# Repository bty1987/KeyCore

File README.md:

<div align="center">

# KeyCore · 磁轴透明屏幕键盘

**67 键磁悬浮轴体 · 13.3" 屏下显示 · 无机械轴 · 全开源**

`磁轴键盘` `Hall Effect` `ESP32-S3` `Transparent Keyboard` `Flux Keyboard 复刻` `嘉立创EDA`

*Finalmouse/Flux 式屏下键盘的国产开源复刻与再设计*

**屏下显示最终效果** —— 13.3" 屏幕实际显示画面：67 键位图 · 按键按下高亮 · 大时钟动效
（预览页 [keymap.html](04-显示层/keymap.html)，正式版为定制全屏程序）

<br clear="all" />

**PCB v43b-5c 封板版布线** —— 300×192mm 四层（L1 红 / L2 蓝 / GND+3V3 平面）：67 霍尔 · 9×74HC4051 · ESP32-S3 · DRC 全绿

</div>

---

## 📖 这是什么

一块 **300×192mm 的透明键盘**：PCB 上密布 67 颗霍尔传感器，键帽底部嵌磁铁，
按下时磁场变化被感应——**没有机械轴体，按压行程就是磁场行程**。
键盘上方悬浮一块 13.3" 1080P 屏幕（屏下键盘结构），显示内容完全可编程。

灵感来自 [Finalmouse x Wooting 的 Flux Keyboard](01-方案/竞品拆解-FluxKeyboard.md)，
本项目是其国产化开源复刻 + 再设计：磁路自主设计、电子自主绘制、结构参数化生成。

```
┌─────────────────────────────────────┐
│   13.3" 透明屏（显示：键位/宏/动画）  │ ← z 7.2+
│─────────────────────────────────────│
│   透明厚板 9mm（67 键孔打穿+磁道）    │ ← z 10.7+
│─────────────────────────────────────│
│   PCB 300×192 4层                    │
│   67×霍尔 + 9×多路开关 + ESP32-S3    │ ← z 0~1.6
│─────────────────────────────────────│
│   底壳（USB-C/背墙通道/12V）          │
└─────────────────────────────────────┘
   按压 → 键帽磁铁靠近霍尔 → ADC 采样 → 触发
```

## ✨ 核心特性

- **磁轴无接触**：HAL49ESO 霍尔 ×67，模拟量采样 → 触发力度/行程软件可调（类 Wooting 模拟轴）
- **9× 74HC4051 分时复用**：67 路模拟信号仅占 1 个 ADC 通道 + 12 个控制脚
- **4 层板电源架构**：内层整平面 GND/3V3 + 191 个缝合孔，67 颗霍尔供电零妥协
- **结构全参数化**：键位表 → OpenSCAD → 厚板 CNC 图纸 / 订购图，改键位即改结构件
- **屏下显示可编程**：定制全屏程序（非浏览器方案），显示键位图/宏状态/力度可视化

## 📊 关键参数

| 项 | 规格 |
|---|---|
| 配列 | 65% 标准配列 61 键 + 宏 M1~M6（共 67） |
| 主控 | ESP32-S3-WROOM-1-N4R8（4MB Flash + 8MB Octal PSRAM, WiFi+BLE） |
| 传感 | HAL49ESO 线性霍尔 ×67（SOT-23，1.9mm 间距采样） |
| 采样链 | 74HC4051 ×9（MUX_A/B/C 地址 + EN_1~9 使能）→ ESP32 ADC |
| PCB | 300.2 × 192 × 1.6mm，4 层（TOP/In1-GND/In2-3V3/BOT），JLC 有铅喷锡 |
| 结构 | 透明亚克力厚板 300.2×192×9mm，67 键孔打穿 + 73 条磁道（CNC） |
| 显示 | 13.3" IPS 1080P（300.2×187.4×2.5mm，HDMI 驱动板 / 计划 Orange Pi 直驱） |
| 接口 | USB-C（数据+5V）、UART 排针、DS18B20 温度探头座、12V 屏供电 |
| 触发 | 磁铁 4×2×2 N52 ×2/键 嵌键帽侧壁（磁路 v5.3，P0′ 实测待做） |

## 🗂 仓库结构

```
KeyCore/
├── 00-文档/          # 项目文档（v3.0 时代已标注存档）
├── 01-方案/          # 方案演进（Flux 竞品拆解、侧磁方案决策）
├── 02-结构图纸/      # ★ OpenSCAD 参数化结构（厚板 v4 / 底壳 / 键位表 CSV）
├── 03-固件/          # ESP32 固件工程（P0 验证完成，正式固件开发中）
├── 04-显示层/        # 屏幕显示页（键位图/坏点测试）
├── 06-测试记录/      # P0 磁路实测数据与报告
├── 07-PCB/           # ★ PCB 交付物（Gerber/打板清单/BOM/全程总结）
│   ├── footprints/   #   封装库
│   ├── tools/        #   处理脚本（历史 KiCad 管线，已退役）
│   └── output/       #   ★★ 所有交付文档都在这里
└── 99-归档/          # 历史方案存档
```

## 📍 项目状态

```mermaid
timeline
    title KeyCore 研发时间线
    2026-09 : 磁路 P0 单键验证 → PASS（隔屏 Δ+1023mV）
    2026-10 上旬 : 侧磁方案 v5.0 定稿 · PCB 300×192 四层布线完成
    2026-10-08 : Gerber 锁定 · 嘉立创下单（5 片全贴 ¥1235）
    2026-10-14 : PCB 到货 → 收板自检（自检固件就绪）
    下一步 : 上电自检 → 固件开发 · 厚板 CNC · 磁轴 P0′ 实测 · 整机合装
```

<details>
<summary><b>已完成里程碑</b>（点击展开）</summary>

- ✅ **P1 屏幕验收**：13.3" 屏 + 驱动板点亮，实测三围与显示区
- ✅ **P0 磁路验证**：隔屏检测可行、极性双向响应、邻域噪声 ±4mV（`06-测试记录/`）
- ✅ **BOM 闭环**：105 元件全部绑定立创 C 号，封装逐项对照商城实物核验
- ✅ **机械定稿**：PCB 300×192 = 厚板同宽 = 屏幕同宽三件套对齐；键位坐标 EDA 实测基准
- ✅ **布线**：FreeRouting 全局布线（GND/3V3 走内层平面 + 191 缝合孔），DRC 仅剩 1 项已接受项
- ✅ **下单**：订单 Y4，生产稿已确认，10-13 发货

</details>

## 🛠 技术栈与工具链

| 层 | 工具 |
|---|---|
| EDA | 嘉立创EDA专业版 4.1.60 + [easyeda-agent](https://github.com/zhoushoujianwork/easyeda-agent) CLI 自动化 |
| 布线 | FreeRouting 1.9.0（DSN 剔除电源网 → SES 回导） |
| 结构 | OpenSCAD（参数化：键位 CSV → 板/壳/订购图） |
| 固件 | PlatformIO + arduino-esp32 / ESP-IDF |
| 验证 | Gerber 机检脚本 · DRC 双口径（几何终审 + 引擎审计） |

## 📚 权威文档（新读者按此顺序读）

1. [画线总结-过程与经验](07-PCB/output/画线总结-过程与经验-20261008.md) —— 全流程 SOP + 18 条踩坑 + 费用实测
2. [设计说明-KeyCore总装](07-PCB/output/设计说明-KeyCore总装-20261007.md) —— 层叠/分区/引脚定稿
3. [打板清单](07-PCB/output/打板清单-KeyCore-v43b-3c-20261008.md) —— BOM 14 项 C 号 + 自留件 + 费用
4. [thickplate-v4.scad](02-结构图纸/thickplate-v4.scad) —— 厚板加工源（67 孔打穿版）

## 💰 成本实况

| 阶段 | 花费 |
|---|---|
| P0/P1 验证（屏+霍尔+磁铁样品） | ~¥470 |
| PCB 4 层 ×5 + SMT 全贴（本单） | ¥1235.19 |
| 厚板 CNC（待下） | 预估 ¥100~200 |
| **首台物料合计** | **~¥2000**（定型后单台 BOM ≈¥1250） |

## 🗺 Roadmap

- [x] P0 磁路验证 · P1 屏幕验收
- [x] PCB 布线 + 下单（v43b-3c）· 收板（10-14）
- [ ] **上电自检**（清单+固件就绪：[收板上电自检](06-测试记录/收板上电自检-20261014.md)）→ 固件（octal PSRAM / 霍尔扫描 / USB HID）
- [ ] 厚板 CNC 下单（图纸就绪：[厚板订购图 V6r](07-PCB/output/厚板订购图-V6-打穿版-20261007.svg)）
- [ ] 磁轴 P0′ 三项实测（回弹/串扰/隔屏Δ）→ 键帽块 P3 设计
- [ ] 屏幕方案落地（Orange Pi Zero 2W + 定制全屏程序）
- [ ] v2 候选：74HC4067 精简（9→5 颗）· ESP32-P4 直驱屏幕 · N16R8V 模组

## 🤝 说明

- 本项目为个人研发项目，过程文档全量保留（包括失败与返工），供同样想做磁轴键盘的玩家参考
- 复刻请重读 [画线总结](07-PCB/output/画线总结-过程与经验-20261008.md) 的"踩坑全集"——每一条都是真实返工换来的
- 嘉立创按图生产不纠错：**DFM 放行 ≠ 设计正确**，正确性唯一来源是数据手册比对与实测

---

<div align="center">

*键盘的尽头是磁场 · Magnetic or nothing*

</div>

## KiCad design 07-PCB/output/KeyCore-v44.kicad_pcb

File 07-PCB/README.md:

# 07-PCB · PCB 工作目录

> **⚠ 2026-10-08 更新**：KiCad 程序化生成管线（tools/ 下的 emit_v4x 等）为历史方案，**现行流程 = 立创EDA 专业版 + easyeda-agent CLI**（FreeRouting 全局布线）。KiCad 管线退役存档于 git 历史。

## 现行状态

- **工程**：KeyCore-v43b-3c（立创EDA，4 层 300×192mm）
- **已下单**：订单 Y4 / SMT2610080582（¥1235.19，5 片全贴，2026-10-13 发货）
- **Gerber**：`output/gerber_3c/KeyCore-v43b-3c-JLC-Order.zip`（18 文件，唯一有效下单包）
- **打板清单**：`output/打板清单-KeyCore-v43b-3c-20261008.md`
- **全程经验**：`output/画线总结-过程与经验-20261008.md`（SOP/踩坑/费用实测）

## 目录

- `footprints/` — KiCad 封装库（早期 KiCad 管线产物，留作参考）
- `tools/` — 退役的 KiCad/SES 处理脚本（git 历史有效，本地可删）
- `output/` — 全部交付物（Gerber/清单/图纸/总结）

## 坐标权威

**EDA live 霍尔位 = 唯一权威**（CSV v5.2 的 x/y 已过时，仅 w_u 键宽列可用）。孔心=霍尔位（2026-10-07 拍板，+4 预放偏置弃用）。

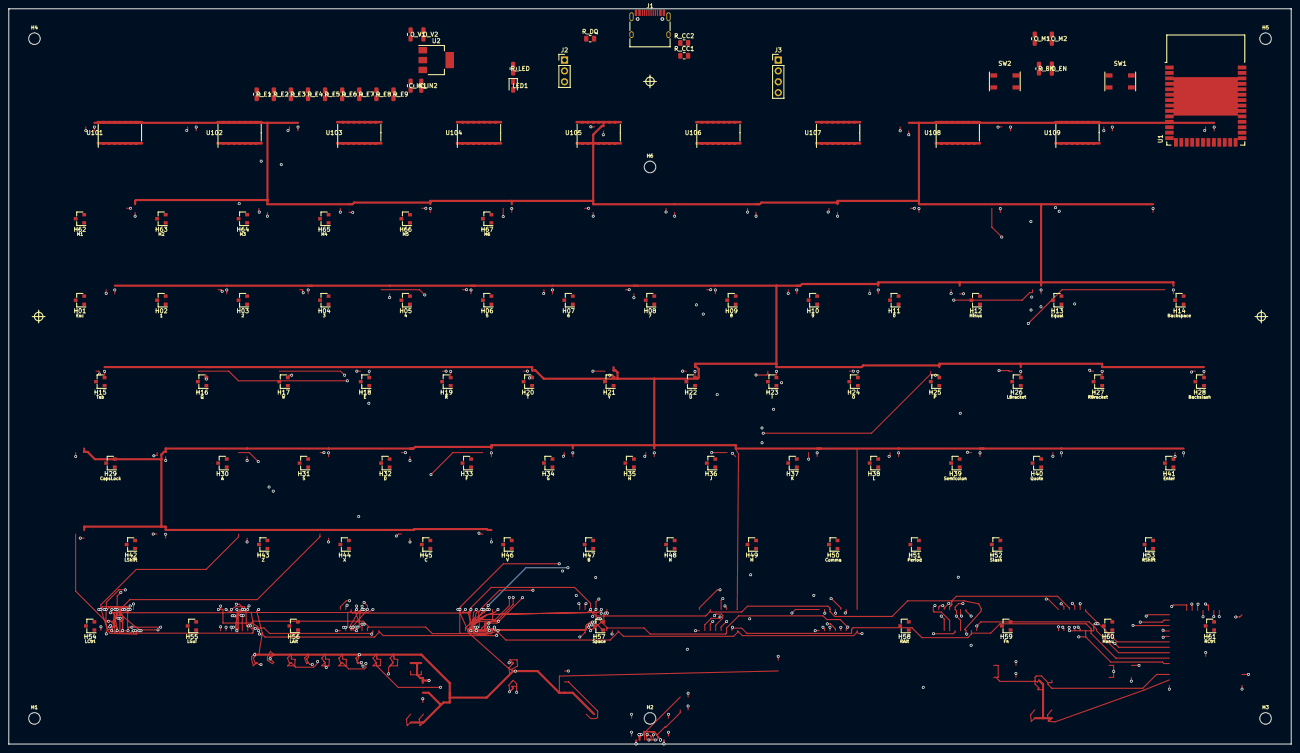
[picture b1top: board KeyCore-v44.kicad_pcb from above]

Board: 4 copper layers, 300.0 x 172.0 mm, 111 parts (0 on the bottom side), 94 nets.

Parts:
C_EN: 10uF; C_0805_2012Metric
C_IN1: 10uF; C_0805_2012Metric
C_IN2: 0.1uF; C_0805_2012Metric
C_M1: 10uF; C_0805_2012Metric
C_M2: 0.1uF; C_0805_2012Metric
C_V1, C_V2: 22uF; C_0805_2012Metric
H01, H02, H03, H04, H05, H06, H07, H08, H09, H10, H11, H12, H13, H14, H15, H16, H17, H18, H19, H20, H21, H22, H23, H24, H25, H26, H27, H28, H29, H30, H31, H32, H33, H34, H35, H36, H37, H38, H39, H40, H41, H42, H43, H44, H45, H46, H47, H48, H49, H50, H51, H52, H53, H54, H55, H56, H57, H58, H59, H60, H61, H62, H63, H64, H65, H66, H67: HAL49E; SOT-23
H1, H2, H3, H4, H5, H6: MountingHole_2.7mm
J1: USB-C 16P; USB_C_Receptacle_HRO_TYPE-C-31-M-12
J2: DS18B20; PinHeader_1x03_P2.54mm_Vertical
J3: UART1; PinHeader_1x04_P2.54mm_Vertical
LED1: PWR; LED_0805_2012Metric
R_CC1, R_CC2: 5.1K; R_0805_2012Metric
R_DQ: 4.7K; R_0805_2012Metric
R_E1, R_E2, R_E3, R_E4, R_E5, R_E6, R_E7, R_E8, R_E9: 10K; R_0805_2012Metric
R_EN: 10K; R_0805_2012Metric
R_LED: 1K; R_0805_2012Metric
SW1: BOOT; Button_Switch_TS-1187A
SW2: EN; Button_Switch_TS-1187A
U1: ESP32-S3-WROOM-1-N4; ESP32-S3-WROOM-1
U2: AMS1117-3.3; SOT-223-3_TabPin2
U101, U102, U103, U104, U105, U106, U107, U108, U109: 74HC4051; SOIC-16_3.9x9.9mm_P1.27mm

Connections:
3V3: C_M1.1, C_M2.1, C_V1.1, C_V2.1, H01.1, H02.1, H03.1, H04.1, H05.1, H06.1, H07.1, H08.1, H09.1, H10.1, H11.1, H12.1, H13.1, H14.1, H15.1, H16.1, H17.1, H18.1, H19.1, H20.1, H21.1, H22.1, H23.1, H24.1, H25.1, H26.1, H27.1, H28.1, H29.1, H30.1, H31.1, H32.1, H33.1, H34.1, H35.1, H36.1, H37.1, H38.1, H39.1, H40.1, H41.1, H42.1, H43.1, H44.1, H45.1, H46.1, H47.1, H48.1, H49.1, H50.1, H51.1, H52.1, H53.1, H54.1, H55.1, H56.1, H57.1, H58.1, H59.1, H60.1, H61.1, H62.1, H63.1, H64.1, H65.1, H66.1, H67.1, J2.1, J3.3, LED1.1, R_DQ.2, R_E1.2, R_E2.2, R_E3.2, R_E4.2, R_E5.2, R_E6.2, R_E7.2, R_E8.2, R_E9.2, R_EN.2, U1.2, U2.2, U101.16, U102.16, U103.16, U104.16, U105.16, U106.16, U107.16, U108.16, U109.16
BOOT: SW1.1, SW1.2, U1.27
CC1: J1.A5, R_CC1.1
CC2: J1.B5, R_CC2.1
EN: C_EN.1, R_EN.1, SW2.1, SW2.2, U1.3
EN_1: R_E1.1, U1.12, U101.6
EN_2: R_E2.1, U1.17, U102.6
EN_3: R_E3.1, U1.18, U103.6
EN_4: R_E4.1, U1.19, U104.6
EN_5: R_E5.1, U1.20, U105.6
EN_6: R_E6.1, U1.21, U106.6
EN_7: R_E7.1, U1.22, U107.6
EN_8: R_E8.1, U1.8, U108.6
EN_9: R_E9.1, U1.9, U109.6
GND: C_EN.2, C_IN1.1, C_IN2.1, C_M1.2, C_M2.2, C_V1.2, C_V2.2, H01.2, H02.2, H03.2, H04.2, H05.2, H06.2, H07.2, H08.2, H09.2, H10.2, H11.2, H12.2, H13.2, H14.2, H15.2, H16.2, H17.2, H18.2, H19.2, H20.2, H21.2, H22.2, H23.2, H24.2, H25.2, H26.2, H27.2, H28.2, H29.2, H30.2, H31.2, H32.2, H33.2, H34.2, H35.2, H36.2, H37.2, H38.2, H39.2, H40.2, H41.2, H42.2, H43.2, H44.2, H45.2, H46.2, H47.2, H48.2, H49.2, H50.2, H51.2, H52.2, H53.2, H54.2, H55.2, H56.2, H57.2, H58.2, H59.2, H60.2, H61.2, H62.2, H63.2, H64.2, H65.2, H66.2, H67.2, J1.A1, J1.A12, J1.B1, J1.B12, J1.S1, J2.3, J3.4, R_CC1.2, R_CC2.2, SW1.3, SW1.4, SW2.3, SW2.4, U1.1, U1.40, U1.41, U2.1, U101.7, U101.8, U102.7, U102.8, U103.7, U103.8, U104.7, U104.8, U105.7, U105.8, U106.7, U106.8, U107.7, U107.8, U108.7, U108.8, U109.7, U109.8
HO_K01: H01.3, U103.13
HO_K02: H02.3, U103.14
HO_K03: H03.3, U103.15
HO_K04: H04.3, U103.12
HO_K05: H05.3, U103.1
HO_K06: H06.3, U103.5
HO_K07: H07.3, U103.2
HO_K08: H08.3, U103.4
HO_K09: H09.3, U104.13
HO_K10: H10.3, U104.14
HO_K11: H11.3, U104.15
HO_K12: H12.3, U104.12
HO_K13: H13.3, U104.1
HO_K14: H14.3, U104.5
HO_K15: H15.3, U105.13
HO_K16: H16.3, U105.14
HO_K17: H17.3, U105.15
HO_K18: H18.3, U105.12
HO_K19: H19.3, U105.1
HO_K20: H20.3, U105.5
HO_K21: H21.3, U105.2
HO_K22: H22.3, U105.4
HO_K23: H23.3, U106.13
HO_K24: H24.3, U106.14
HO_K25: H25.3, U106.15
HO_K26: H26.3, U106.12
HO_K27: H27.3, U106.1
HO_K28: H28.3, U106.5
HO_K29: H29.3, U107.13
HO_K30: H30.3, U107.14
HO_K31: H31.3, U107.15
HO_K32: H32.3, U107.12
HO_K33: H33.3, U107.1
HO_K34: H34.3, U107.5
HO_K35: H35.3, U107.2
HO_K36: H36.3, U107.4
HO_K37: H37.3, U108.13
HO_K38: H38.3, U108.15
HO_K39: H39.3, U108.1
HO_K40: H40.3, U108.2
HO_K41: H41.3, U108.4
HO_K42: H42.3, U109.13
HO_K43: H43.3, U109.14
HO_K44: H44.3, U109.15
HO_K45: H45.3, U109.12
HO_K46: H46.3, U109.1
HO_K47: H47.3, U109.5
HO_K48: H48.3, U109.2
HO_K49: H49.3, U109.4
HO_K50: H50.3, U108.14
HO_K51: H51.3, U108.12
HO_K52: H52.3, U108.5
HO_K53: H53.3, U106.4
HO_K54: H54.3, U101.14
HO_K55: H55.3, U101.12
HO_K56: H56.3, U102.13
HO_K57: H57.3, U102.14
HO_K58: H58.3, U102.15
HO_K59: H59.3, U102.12
HO_K60: H60.3, U102.1
HO_K61: H61.3, U102.5
HO_K62: H62.3, U101.13
HO_K63: H63.3, U101.15
HO_K64: H64.3, U101.1
HO_K65: H65.3, U101.5
HO_K66: H66.3, U101.2
HO_K67: H67.3, U101.4
LED: R_LED.2, U1.38
LED_A: LED1.2, R_LED.1
MUX_A: U1.5, U101.11, U102.11, U103.11, U104.11, U105.11, U106.11, U107.11, U108.11, U109.11
MUX_B: U1.6, U101.10, U102.10, U103.10, U104.10, U105.10, U106.10, U107.10, U108.10, U109.10
MUX_C: U1.7, U101.9, U102.9, U103.9, U104.9, U105.9, U106.9, U107.9, U108.9, U109.9
ONE_WIRE: J2.2, R_DQ.1, U1.23
U1RX: J3.2, U1.11
U1TX: J3.1, U1.10
USB_DN: J1.A7, J1.B7, U1.13
USB_DP: J1.A6, J1.B6, U1.14
VBUS: C_IN1.2, C_IN2.2, J1.A4, J1.A9, J1.B4, J1.B9, U2.3
Z_COM: U101.3, U102.3, U103.3, U104.3, U105.3, U106.3, U107.3, U108.3, U109.3

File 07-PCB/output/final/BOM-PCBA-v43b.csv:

Comment,Designator,Footprint,LCSC Part Number
10uF,"C_EN,C_IN1,C_M1",C_0805_2012Metric,C15850
0.1uF,"C_IN2,C_M2",C_0805_2012Metric,C49678
22uF,"C_V1,C_V2",C_0805_2012Metric,C45783
HAL49E,"H01,H02,H03,H04,H05,H06,H07,H08,H09,H10,H11,H12,H13,H14,H15,H16,H17,H18,H19,H20,H21,H22,H23,H24,H25,H26,H27,H28,H29,H30,H31,H32,H33,H34,H35,H36,H37,H38,H39,H40,H41,H42,H43,H44,H45,H46,H47,H48,H49,H50,H51,H52,H53,H54,H55,H56,H57,H58,H59,H60,H61,H62,H63,H64,H65,H66,H67",SOT-23,C7420984
USB-C 16P,J1,USB_C_Receptacle_HRO,
PinHeader 1x3 (手焊),J2,PinHeader_1x03_P2.54,
PinHeader 1x4 (手焊),J3,PinHeader_1x04_P2.54,
LED 绿色 0805,LED1,LED_0805_2012Metric,C965812
5.1K,"R_CC1,R_CC2",R_0805_2012Metric,C27834
4.7K,R_DQ,R_0805_2012Metric,C17673
10K,"R_E1,R_E2,R_E3,R_E4,R_E5,R_E6,R_E7,R_E8,R_E9,R_E10",R_0805_2012Metric,C25804
1K,R_LED,R_0805_2012Metric,C17513
BOOT 按键 (手焊),SW1,Button_Switch_TS-118,
EN 按键 (手焊),SW2,Button_Switch_TS-118,
ESP32-S3-WROOM-1-N4,U1,ESP32-S3-WROOM-1,C2913197
AMS1117-3.3,U2,SOT-223-3_TabPin2,C6186
74HC4051,"U101,U102,U103,U104,U105,U106,U107,U108,U109",SOIC-16_3.9x9.9mm_P1.27mm,C2943297

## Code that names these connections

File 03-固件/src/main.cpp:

// ============================================================
// KeyCore 收板自检固件 (bring-up) · 2026-10-14
// 目的: PCB (订单 Y4, 10-14 到货) 上电第一支固件——
//       验证主控 / 8MB Octal PSRAM / LED1 / 67 路霍尔采样链是否全通
//
// 烧录: pio run -t upload -e bringup && pio run -t monitor -e bringup
//       (USB-C 即 USB-Serial-JTAG; 进不去下载模式时按住 BOOT=SW1 再插 USB)
//
// 串口判定 (115200):
//   芯片    = ESP32-S3
//   Flash   = 4 MB
//   PSRAM   = 8388608 bytes (8MB, OPI) + 读写 OK   ← 认不到就是 memory_type 没开 qio_opi
//   LED1    = 红光, 每 0.5s 闪 (硬件带 y155~172, USB 口旁)
//   扫描    = 每轮 9×8=72 通道: ok 格 ≈1650mV 上下 (HAL49ESO 零场 ≈ VCC/2)
//             其中 ≥67 格在 1290~2100mV 内; 空通道(72-67=5 个)数值不定属正常
//   磁铁测试: 逐键靠近键位 → 串口弹 ALERT 行 (Δ>60mV), mV 单向变化 = 采样链全通
//   基线    = 上电静置取均值; 串口发任意字符重取 (比如拿磁铁扫完一圈后)
//
// 引脚出处: 设计说明-KeyCore总装 §功能引脚分配 + 03-固件/README 定稿备忘
//   ADC = IO4 ✅已核实: U1 typed 网络表 pad4 = "Z_F"(9×4051 Z 汇聚→RC→ADC1)
//   MUX_A/B/C = IO5/6/7; EN_1..EN_9 = IO8~16 顺序对应 ✅(U1 网络表+41 脚表交叉推导自洽:
//   pad8=IO15=EN_8, pad9=IO16=EN_9, pad12=IO8=EN_1 … pad22=IO14=EN_7)
//   IO21 = ONE_WIRE (J2 未装排针 → 不碰, 禁死等); IO35/36/37 = PSRAM 保留, 禁用; IO1/IO2 板上接 GND
// ============================================================

#include <Arduino.h>
#include <esp_flash.h>

static const int PIN_ADC    = 4;
static const int PIN_MUX_A  = 5;
static const int PIN_MUX_B  = 6;
static const int PIN_MUX_C  = 7;
static const int PIN_EN[9]  = {8, 9, 10, 11, 12, 13, 14, 15, 16};  // EN_1..EN_9, 低有效
static const int PIN_LED1   = 38;

static const long MV_MIN_OK = 1290;   // 零场 ≈1650mV; 低于此=对地短路/未供
static const long MV_MAX_OK = 2100;   // 高于此=悬空/对电源短路
static const long MV_DELTA_ALERT = 60; // 与基线差超此值 → ALERT (P0 实测噪声 ±4mV, 60 足够安全)

static long base_mv[9][8];
static long last_mv[9][8];

static long read_adc_mv() {
  analogReadMilliVolts(PIN_ADC);        // 换通道首样弃掉 (100Ω+100nF RC 建立)
  delayMicroseconds(300);
  long s = 0;
  for (int i = 0; i < 8; i++) { s += analogReadMilliVolts(PIN_ADC); delayMicroseconds(50); }
  return s / 8;
}

static void all_en_off() { for (int i = 0; i < 9; i++) digitalWrite(PIN_EN[i], HIGH); }

static void select_ch(int mux, int ch) {
  all_en_off();
  digitalWrite(PIN_MUX_A, ch & 1 ? HIGH : LOW);
  digitalWrite(PIN_MUX_B, ch & 2 ? HIGH : LOW);
  digitalWrite(PIN_MUX_C, ch & 4 ? HIGH : LOW);
  digitalWrite(PIN_EN[mux], LOW);       // 低有效, 只开当前这一片
}

static void sweep(long out[9][8]) {
  for (int m = 0; m < 9; m++)
    for (int c = 0; c < 8; c++) { select_ch(m, c); out[m][c] = read_adc_mv(); }
  all_en_off();
}

static void take_baseline() {
  sweep(last_mv);                        // 首扫弃掉 (MUX/RC 稳定)
  for (int r = 0; r < 4; r++) {          // 4 轮均值当基线
    sweep(last_mv);
    for (int m = 0; m < 9; m++)
      for (int c = 0; c < 8; c++) base_mv[m][c] = (r == 0) ? last_mv[m][c]
                                              : (base_mv[m][c] + last_mv[m][c]) / 2;
  }
}

void setup() {
  pinMode(PIN_LED1, OUTPUT);
  for (int i = 0; i < 9; i++) { pinMode(PIN_EN[i], OUTPUT); digitalWrite(PIN_EN[i], HIGH); }
  pinMode(PIN_MUX_A, OUTPUT); pinMode(PIN_MUX_B, OUTPUT); pinMode(PIN_MUX_C, OUTPUT);

  Serial.begin(115200);
  delay(2000);                           // 电源/RC 静置
  Serial.println();
  Serial.println("======== KeyCore 收板自检 ========");

  Serial.printf("芯片   : %s rev%d @ %u MHz\n",
                ESP.getChipModel(), ESP.getChipRevision(), ESP.getCpuFreqMHz());

  uint32_t flash_kb = 0;
  esp_flash_get_size(NULL, &flash_kb);
  Serial.printf("Flash  : %u KB  (期望 4096 = 4MB)\n", flash_kb);

  bool ps = psramInit();
  Serial.printf("PSRAM  : %s, %u bytes  (期望 8388608 = 8MB OPI; 认不到查 qio_opi)\n",
                ps ? "OK" : "FAIL", ESP.getPsramSize());
  if (ps && ESP.getPsramSize() > 0) {
    uint8_t *buf = (uint8_t *)ps_malloc(4096);
    bool rw = (buf != nullptr);
    if (rw) {
      memset(buf, 0xA5, 4096);
      rw = (buf[0] == 0xA5) && (buf[4095] == 0xA5);
      free(buf);
    }
    Serial.printf("PSRAM 读写: %s\n", rw ? "OK" : "FAIL");
  }

  Serial.printf("ADC 引脚: IO%d (ADC1, 网络 Z_F) —— 若矩阵全 0/全 4095, 优先查采样链供电\n", PIN_ADC);
  Serial.println("LED1 (IO38) 将每 0.5s 闪烁; 串口发任意字符 = 重新取基线");

  take_baseline();
  Serial.println("======== 基线取好, 开始扫描 ========");
}

void loop() {
  static uint32_t sweep_n = 0;

  if (Serial.available()) {
    while (Serial.available()) Serial.read();
    take_baseline();
    Serial.println(">> 基线已更新");
  }

  sweep(last_mv);
  sweep_n++;

  int ok = 0, alerts = 0;
  for (int m = 0; m < 9; m++)
    for (int c = 0; c < 8; c++) {
      long v = last_mv[m][c];
      if (v >= MV_MIN_OK && v <= MV_MAX_OK) ok++;
      long d = v - base_mv[m][c];
      if (abs(d) > MV_DELTA_ALERT) { alerts++; Serial.printf("ALERT EN%d ch%d = %ldmV (Δ%+ld)\n", m + 1, c, v, d); }
    }
  Serial.printf("sweep#%u  ok=%d/72  alert=%d\n", sweep_n, ok, alerts);

  if (sweep_n % 8 == 0) {               // ~每 5s 打一轮完整矩阵
    Serial.println("-- 通道矩阵 mV (EN行 × ch列) --");
    for (int m = 0; m < 9; m++) {
      Serial.printf("EN%d:", m + 1);
      for (int c = 0; c < 8; c++) Serial.printf(" %4ld", last_mv[m][c]);
      Serial.println();
    }
  }

  digitalWrite(PIN_LED1, (sweep_n & 1) ? HIGH : LOW);   // 心跳: LED 每 0.5s 翻转
  delay(440);
}

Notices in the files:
README.md:
License: TBD
